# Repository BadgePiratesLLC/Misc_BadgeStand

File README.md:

# Misc_BadgeStand
Powered Stand for holding and running your badge(s)

Build Instructions:
<pic of Built Stand>

Your badge stand shipped with 2 stand bases, one is a blank PCB and the other is populated with Electronics that drop 5v from a micro USB down to 3.3v at the 2 pin locations. Of course one is 3.3v and the other is GND (see Pic below). 

<pic of pins with Labels> (Still needs Added)

Additionally you have 4 stand offs of 2 different sizes, 2 screws and 2 nuts. Use these to connect your 2 Base pieces to each other, using the sizes to adjust the space between the bases.

<Pic or Video of Connecting the Standoffs to Bases>(Still needs Added)

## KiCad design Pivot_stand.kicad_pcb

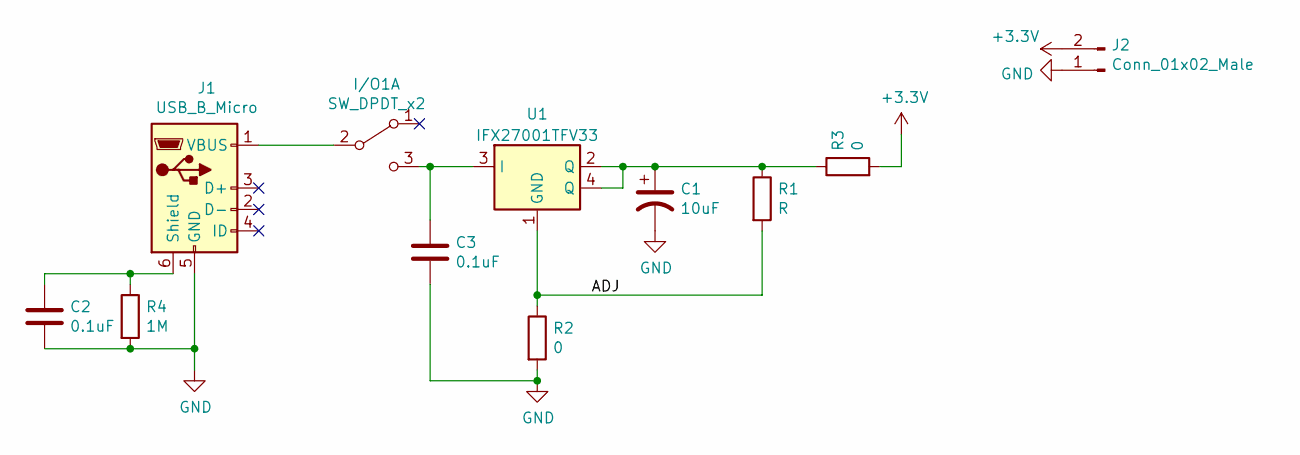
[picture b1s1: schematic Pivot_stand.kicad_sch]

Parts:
C1: 10uF; C_0805_2012Metric
C2, C3: 0.1uF; C_0805_2012Metric
I/O1: SW_DPDT_x2; SW_SPDT_PCM12
J1: USB_B_Micro; USB_Micro-B_Wuerth_629105150521
J2: Conn_01x02_Male; PinHeader_1x02_P2.00mm_Vertical
R1: R; R_1206_3216Metric
R2, R3: 0; R_1206_3216Metric
R4: 1M; R_1206_3216Metric
U1: IFX27001TFV33; SOT-223

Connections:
+3V3: J2.2, R3.2
/ADJ: R1.2, R2.1, U1.1 (GND)
GND: C1.2, C2.2, C3.2, J1.5 (GND), J2.1, R2.2, R4.2
unnamed: C1.1, R1.1, R3.1, U1.2 (Q), U1.4 (Q)
unnamed: C2.1, J1.6 (Shield), R4.1
unnamed: C3.1, I/O1.3 (C), U1.3 (I)
unnamed: I/O1.2 (B), J1.1 (VBUS)

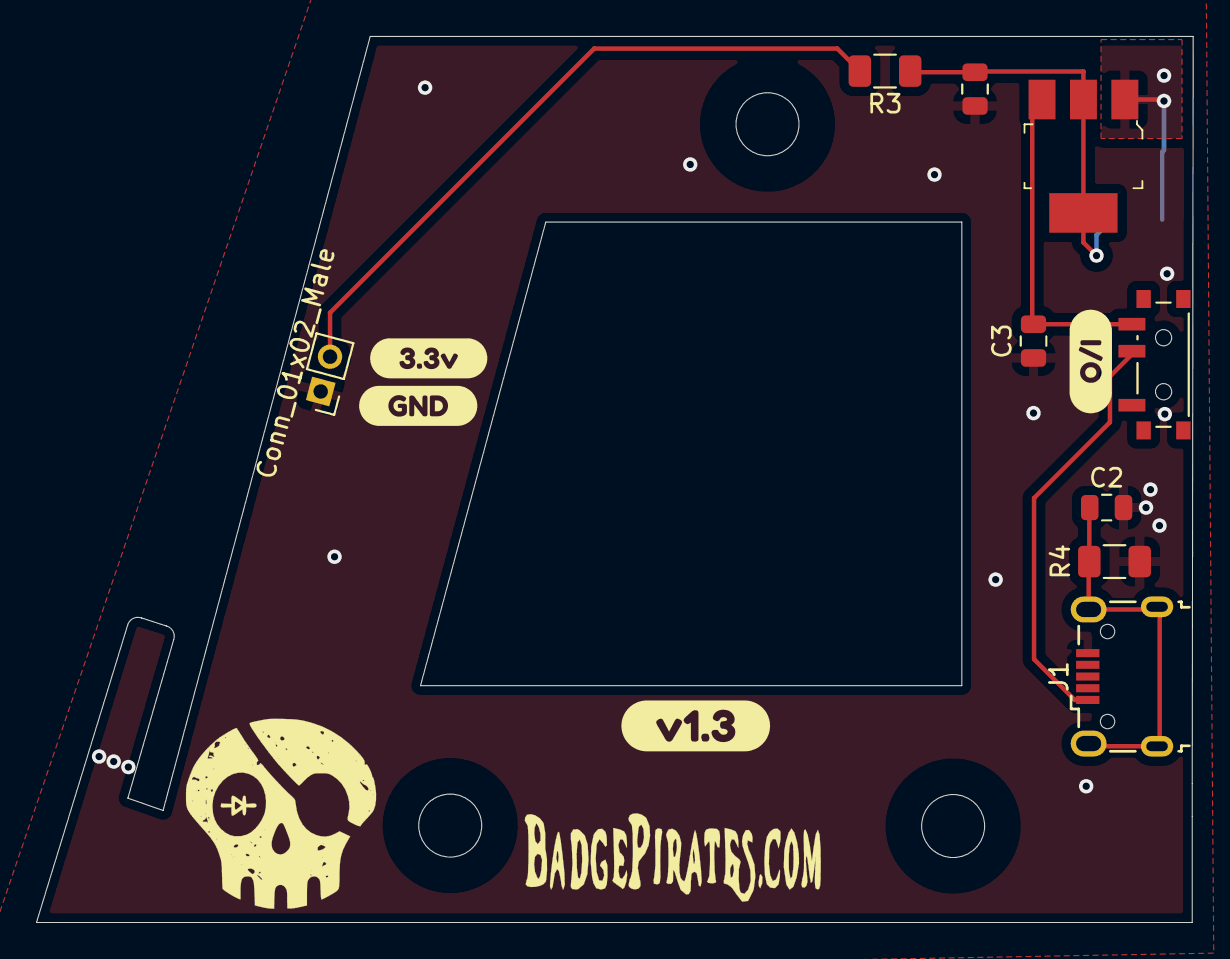
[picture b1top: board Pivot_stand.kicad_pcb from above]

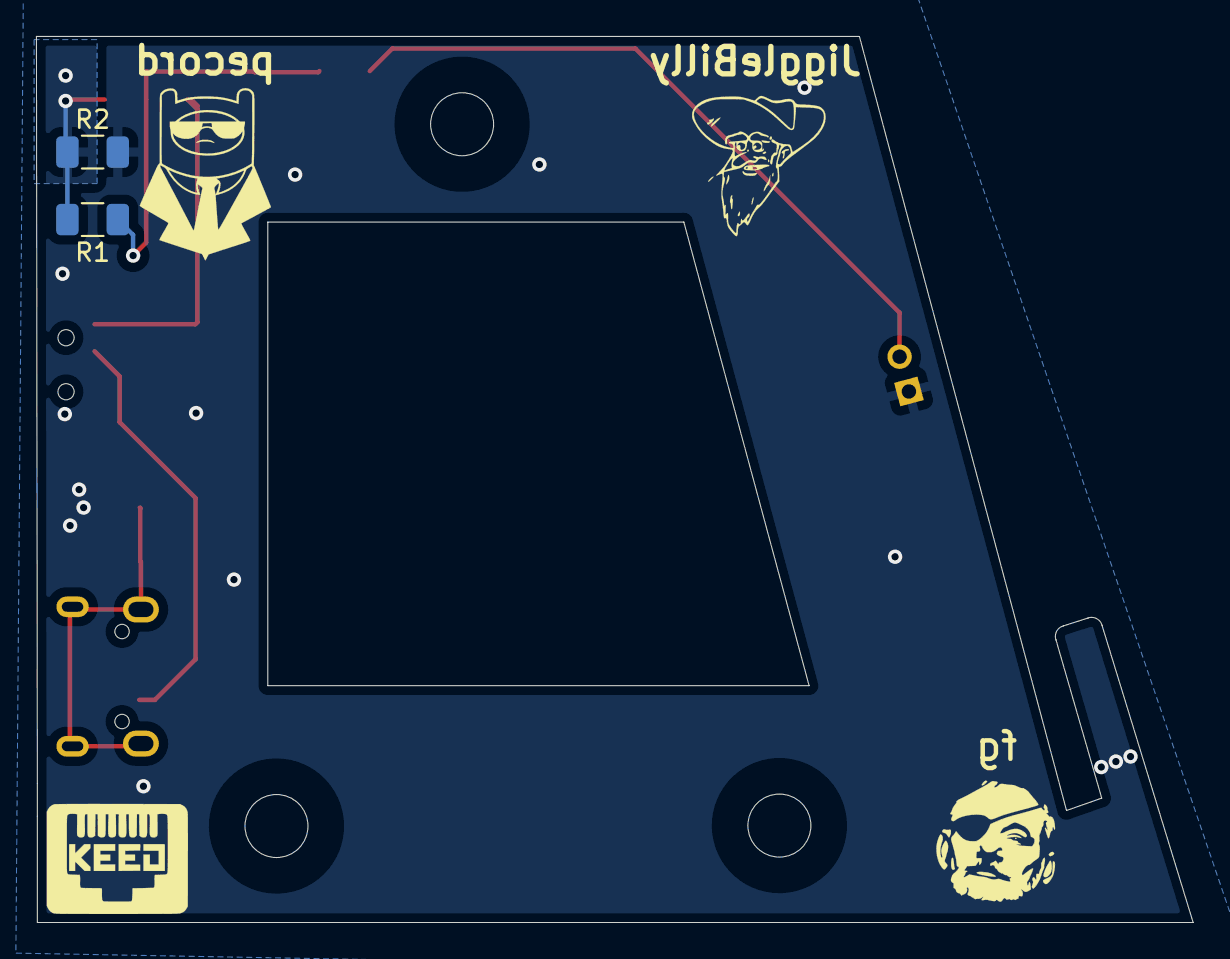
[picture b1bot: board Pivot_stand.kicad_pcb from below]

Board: 2 copper layers, 64.3 x 49.2 mm, 15 parts (2 on the bottom side), 7 nets.

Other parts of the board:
kibuzzard-629C349E: G***; kibuzzard-629C349E
kibuzzard-629C2456: G***; kibuzzard-629C2456
kibuzzard-629C2481: G***; kibuzzard-629C2481
kibuzzard-629C3492: G***; kibuzzard-629C3492

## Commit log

2022-08-01 Create CAD
2022-10-16 Schematic cleanup
    Moved text in schematic to make it more readable
2022-10-16 Improvements
    Added resistor from pin 1 of regulator to ground to allow for Adj regulator to be used. Defaulted to 0 ohm.
    Added 0 ohm resistor to voltage output. This allows a resistance to be added in to protect SAOs with no current limiting resistor on LEDs.
    Tied USB shield to ground using 1M resistor and 0.1uF cap.
2022-10-16 Updated format to KiCad 6
    Updated format to KiCad 6
2022-10-16 Changed Fill
    Changed the fill type from hatched to solid to improve signal integrity
2022-10-16 Changed the regulator symbol
    Changed the regulator symbol to include a 4th pin for the output tab.
2022-10-16 Updated U1 footprint
    Updated the U1 footprint
2022-10-16 Changed footprint library
    Changed footprint library to use the BadgePirtate library
2022-10-16 Change SW1 footprint
    Changed SW1 footprint to use the BP lib
2022-10-16 Fixed ref des
    Fixed I/O ref des
2022-10-16 Ignore auto saved files
    Change .gitignore to include the autosaved files
2022-10-16 Layout updates
    Added new parts to PCB to match schematic changes.
2022-10-27 Cleanup
2022-10-27 Ignore .zip files
